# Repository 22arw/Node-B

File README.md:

# Node-B - Remote Water Quality Sensor
This project utilizes the lightweight Adafruit Feather with LoRaWAN in order to read and broadcast water quality data (such as Temperature, pH level, and Total Dissolved Solids (TDS)) to a central Gateway and Server for public use.

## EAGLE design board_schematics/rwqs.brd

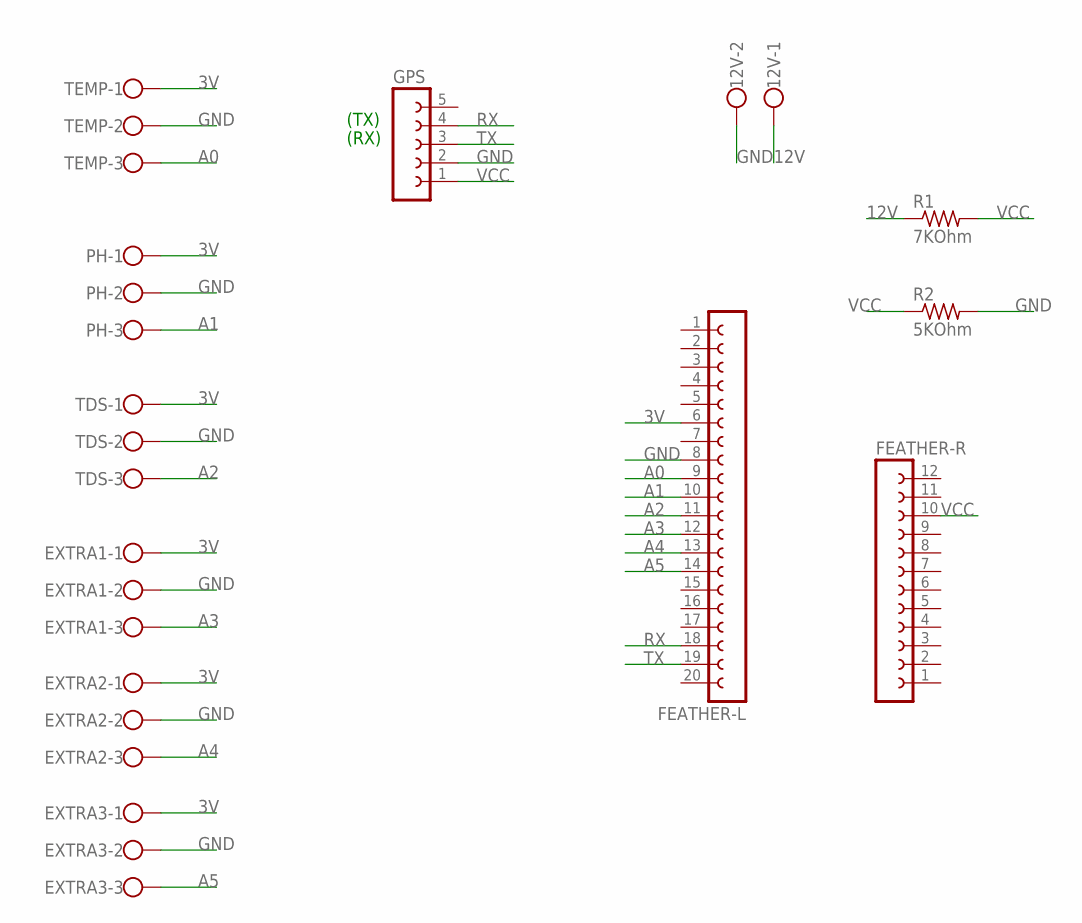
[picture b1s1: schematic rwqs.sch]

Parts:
12V: W237-113
EXTRA1, EXTRA2, EXTRA3: W237-103
FEATHER-L: FE20-1; FE20
FEATHER-R: FE12-1; FE12
GPS: FE05-1
PH: W237-103
R1: 7KOhm; 0204V
R2: 5KOhm; 0204V
TDS: W237-103
TEMP: W237-103

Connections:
3V: EXTRA1.1, EXTRA2.1, EXTRA3.1, FEATHER-L.6, PH.1, TDS.1, TEMP.1
12V: 12V.1, R1.1
A0: FEATHER-L.9, TEMP.3
A1: FEATHER-L.10, PH.3
A2: FEATHER-L.11, TDS.3
A3: EXTRA1.3, FEATHER-L.12
A4: EXTRA2.3, FEATHER-L.13
A5: EXTRA3.3, FEATHER-L.14
GND: 12V.2, EXTRA1.2, EXTRA2.2, EXTRA3.2, FEATHER-L.8, GPS.2, PH.2, R2.2, TDS.2, TEMP.2
RX: FEATHER-L.18, GPS.4
TX: FEATHER-L.19, GPS.3
VCC: FEATHER-R.10, GPS.1, R1.2, R2.1

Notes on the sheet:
(RX)
(TX)

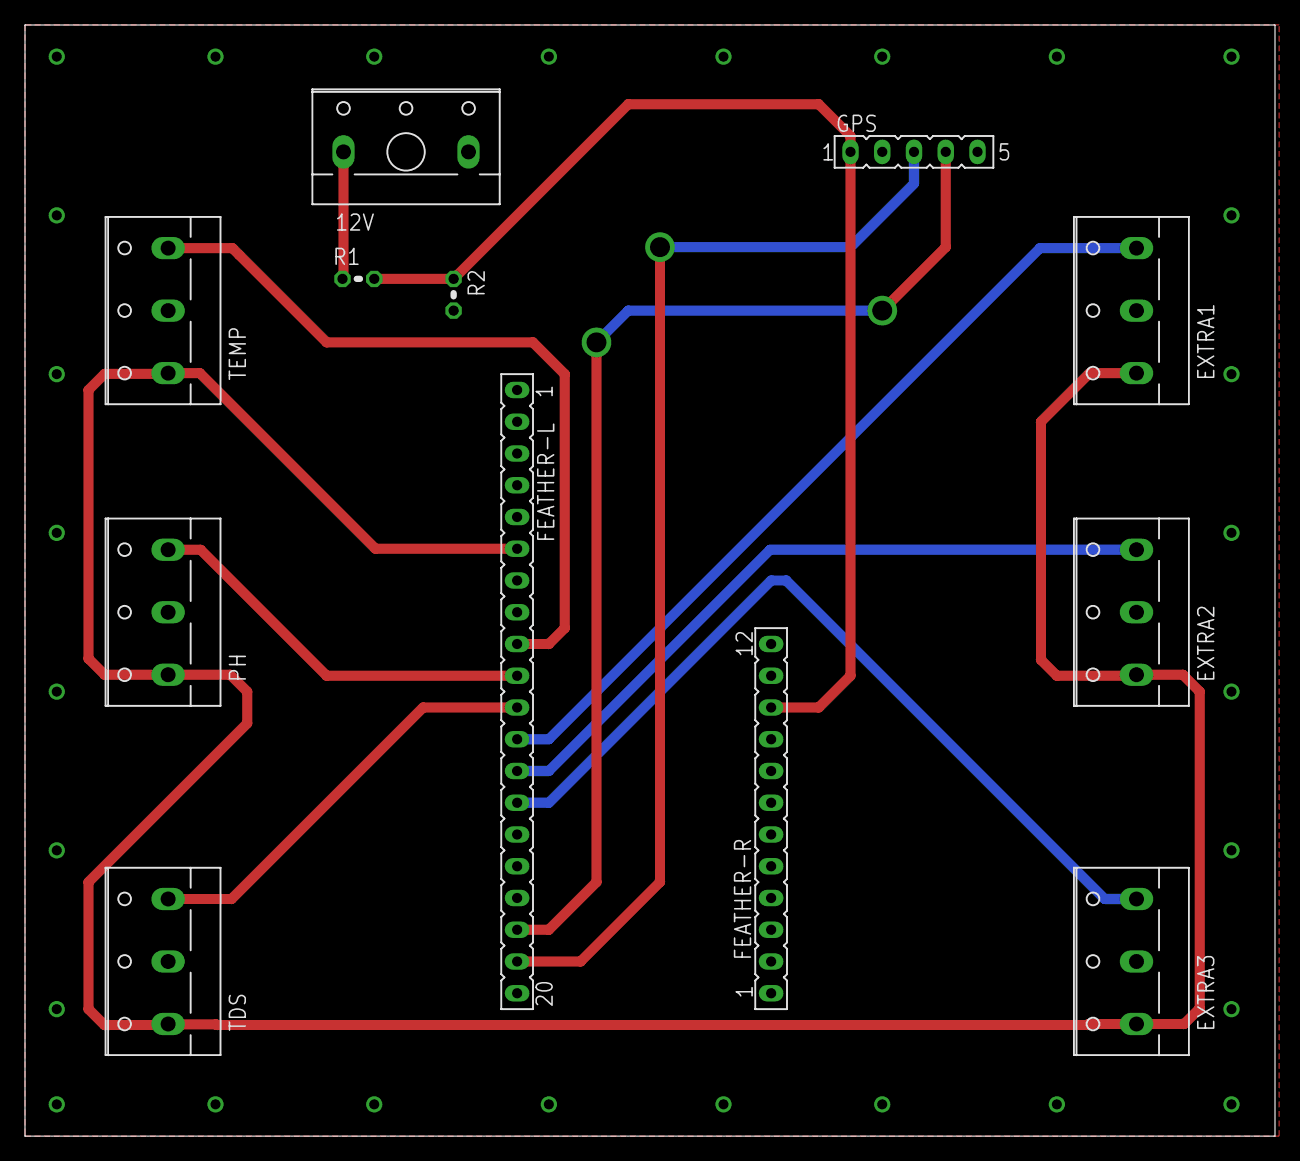
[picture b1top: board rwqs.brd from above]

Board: 2 copper layers, 100.0 x 88.9 mm, 12 parts (0 on the bottom side), 12 nets.

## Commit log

2021-03-01 Initial Commit
    Initial commit of Arduino source code, libraries for Remote Water Quality Sensor from Node B
2021-03-12 Added GPS boilerplate
    Added basic framework for the use of GPS with the Arduino. Also made code style more consistent.
2021-03-12 Created README
2021-05-04 Implemented GPS; Updated Gateway Connection; Reworked pH formula; Cleaned up code
2021-05-04 Added PCB Schematics
2021-05-04 Changed sample times back to normal from testing
